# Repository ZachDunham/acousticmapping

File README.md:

acousticmapping
===============

Data vis, light painting mashup exploring room acoustics 

## Synopsis 
The goal for this project is to be able to photograph standing wave interference to create a kind of acoustical map of a room. Wave interference, simply put, is caused when two waves of the same frequency but different phase combine and result in a waveform that has an increased or decreased amplitude. 

In order to photograph these interference or standing wave patterns, I'm playing a range of sine tones but only working with one frequency at a time in order to isolate these interferences. In any listening situation there are direct and reflected sounds. As sound leaves the source it propagates outward, reflecting off of surfaces along the way, until it reaches your ears. Depending on where you are in the room, some portion of this sound also travels directly to the ear. Because of these alternate routes (reflected and direct) we end up with differences in arrival time which can also mean differences in the phase (angle) of the wave. As these in- or out-of-phase signals reach our ear, they can cancel each other out or combine to result in a larger waveform.

The hardware and software here are part of this ongoing project.  

## Liscense 
In the interest of collaboration and good will, the files herein are offered for public use. Just don't be a jerk about it and credit me if you use it commercially :)

## CONTAINED HEREIN
* Embedded systems design files: Namely .brd, .sch
* Firmware: Arduino sketches

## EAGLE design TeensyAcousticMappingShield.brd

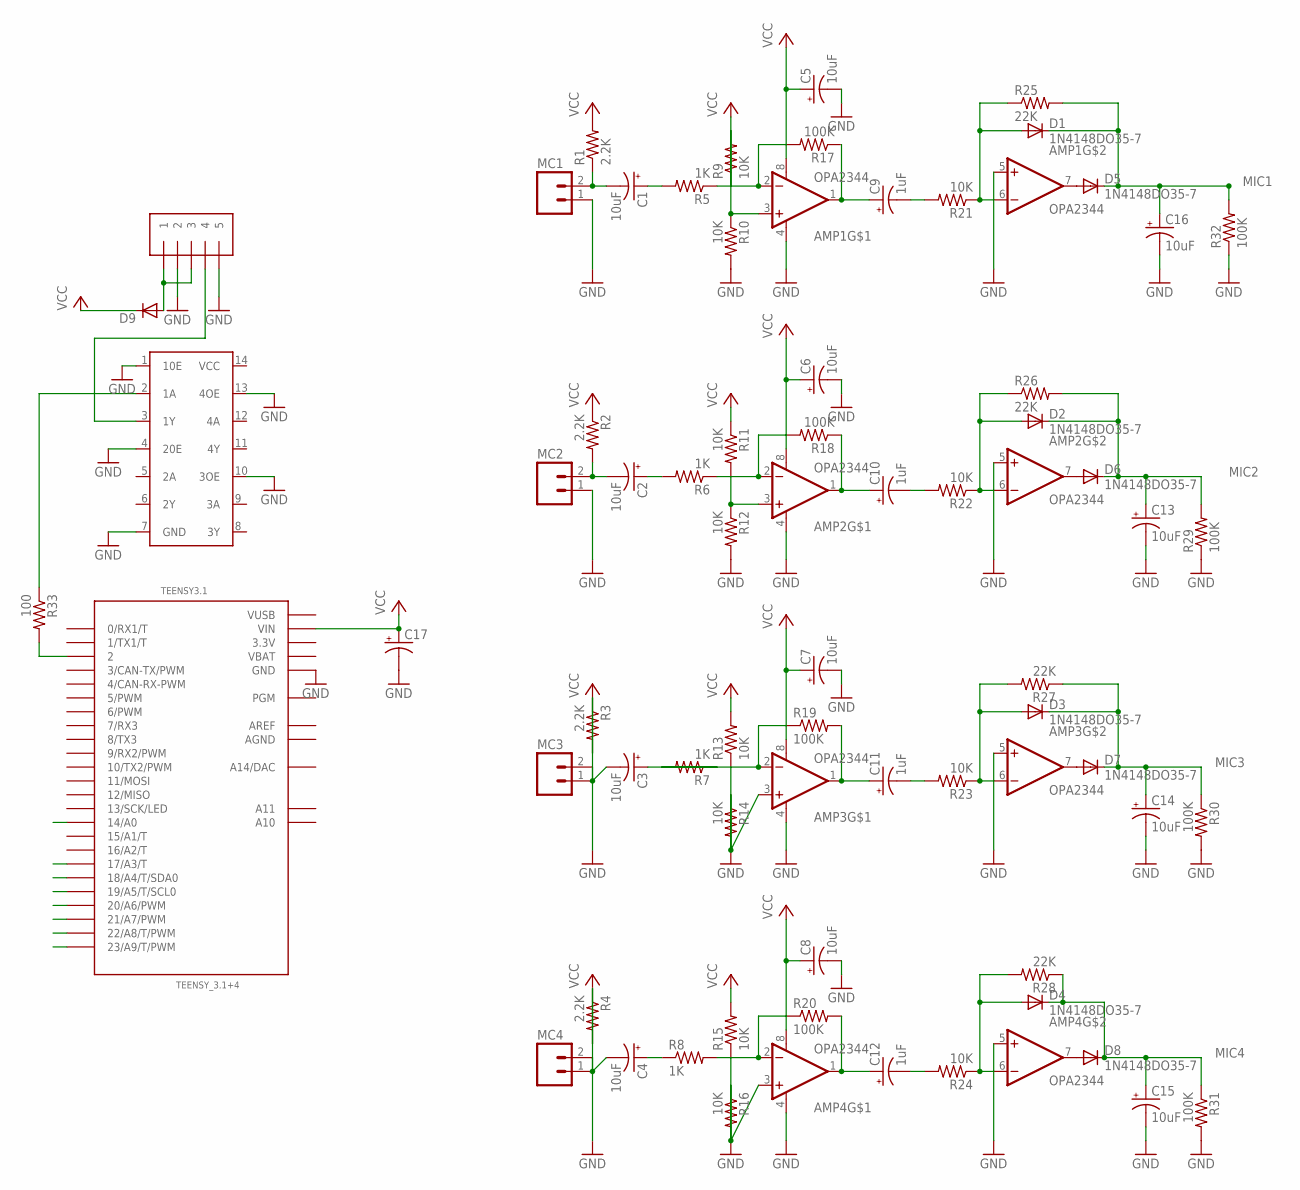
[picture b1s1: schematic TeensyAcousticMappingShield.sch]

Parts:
AMP1, AMP2, AMP3, AMP4: OPA2344; DIP08
C1, C2, C3, C4, C5, C6, C7, C8, C13, C14, C15, C16: 10uF; E2-4
C9, C10, C11, C12: 1uF; E2-4
C17: CPOL-USE2.5-6; E2,5-6
D1, D2, D3, D4, D5, D6, D7, D8: 1N4148DO35-7; DO35-7
D9: DIODE-C1702-05; C1702-05
IO: 1X5; 1X05-3.5MM
LEVELSHIFT: 74AHCT125; DIL14
MC1, MC2, MC3, MC4: M02LOCK_LONGPADS; 1X02_LOCK_LONGPADS
R1, R2, R3, R4: 2.2K; 0207/2V
R5, R6, R7, R8: 1K; 0207/2V
R9, R10, R11, R12, R13, R14, R15, R16, R21, R22, R23, R24: 10K; 0207/2V
R17, R18, R19, R20, R29, R30, R31, R32: 100K; 0207/2V
R25, R26, R27, R28: 22K; 0207/2V
R33: 100; 0207/2V
TEENSY3.1: TEENSY_3.1+4

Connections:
3.3V: TEENSY3.1.3.3V, TEENSY3.1.3.3V1 (3.3V)
AGND: TEENSY3.1.AGND
AREF: TEENSY3.1.AREF
B+: D9.A, IO.1, IO.3
GND: AMP1.4 (V-), AMP1.5 (+IN), AMP2.4 (V-), AMP2.5 (+IN), AMP3.4 (V-), AMP3.5 (+IN), AMP4.4 (V-), AMP4.5 (+IN), C5.-, C6.-, C7.-, C8.-, C13.-, C14.-, C15.-, C16.-, C17.-, IO.2, IO.5, LEVELSHIFT.1 (10E), LEVELSHIFT.4 (20E), LEVELSHIFT.7 (GND), LEVELSHIFT.10 (3OE), LEVELSHIFT.13 (4OE), MC1.1, MC2.1, MC3.2, MC4.2, R10.2, R12.2, R14.1, R16.1, R29.1, R32.1, TEENSY3.1.GND, TEENSY3.1.GND1 (GND)
MIC1: C16.+, D1.C, D5.C, R25.2, R32.2, TEENSY3.1.14/A0
MIC2: C13.+, D2.C, D6.C, R26.2, R29.2, TEENSY3.1.17/A3 (17/A3/T)
MIC3: C14.+, D3.C, D7.C, R27.1, R30.1, TEENSY3.1.18/A4 (18/A4/T/SDA0)
MIC4: C15.+, D4.C, D8.C, R28.1, R31.1, TEENSY3.1.19/A5 (19/A5/T/SCL0)
unnamed: AMP1.3 (+IN), R9.2, R10.1
unnamed: AMP1.2 (-IN), R5.1, R17.2
unnamed: AMP1.1 (OUT), C9.+, R17.1
unnamed: C1.+, R5.2
unnamed: C1.-, MC1.2, R1.1
unnamed: C9.-, R21.2
unnamed: AMP1.6 (-IN), D1.A, R21.1, R25.1
unnamed: AMP1.7 (OUT), D5.A
unnamed: AMP2.3 (+IN), R11.2, R12.1
unnamed: AMP2.2 (-IN), R6.1, R18.2
unnamed: AMP2.1 (OUT), C10.+, R18.1
unnamed: C2.+, R6.2
unnamed: C2.-, MC2.2, R2.2
unnamed: C10.-, R22.2
unnamed: AMP2.6 (-IN), D2.A, R22.1, R26.1
unnamed: AMP2.7 (OUT), D6.A
unnamed: AMP3.3 (+IN), R13.1, R14.2
unnamed: R33.2, TEENSY3.1.2
unnamed: LEVELSHIFT.2 (1A), R33.1
unnamed: AMP3.2 (-IN), R7.2, R19.1
unnamed: AMP3.1 (OUT), C11.+, R19.2
unnamed: C3.+, R7.1
unnamed: C3.-, MC3.1, R3.1
unnamed: C11.-, R23.2
unnamed: AMP3.6 (-IN), D3.A, R23.1, R27.2
unnamed: AMP3.7 (OUT), D7.A
unnamed: AMP4.3 (+IN), R15.1, R16.2
unnamed: AMP4.2 (-IN), R8.2, R20.1
unnamed: AMP4.1 (OUT), C12.+, R20.2
unnamed: C4.+, R8.1
unnamed: C4.-, MC4.1, R4.1
unnamed: C12.-, R24.2
unnamed: AMP4.6 (-IN), D4.A, R24.1, R28.2
unnamed: AMP4.7 (OUT), D8.A
unnamed: IO.4, LEVELSHIFT.3 (1Y)
VBAT: TEENSY3.1.VBAT
VCC: AMP1.8 (V+), AMP2.8 (V+), AMP3.8 (V+), AMP4.8 (V+), C5.+, C6.+, C7.+, C8.+, C17.+, D9.C, R1.2, R2.1, R3.2, R4.2, R9.1, R11.1, R13.2, R15.2, TEENSY3.1.VIN
VUSB: TEENSY3.1.VUSB

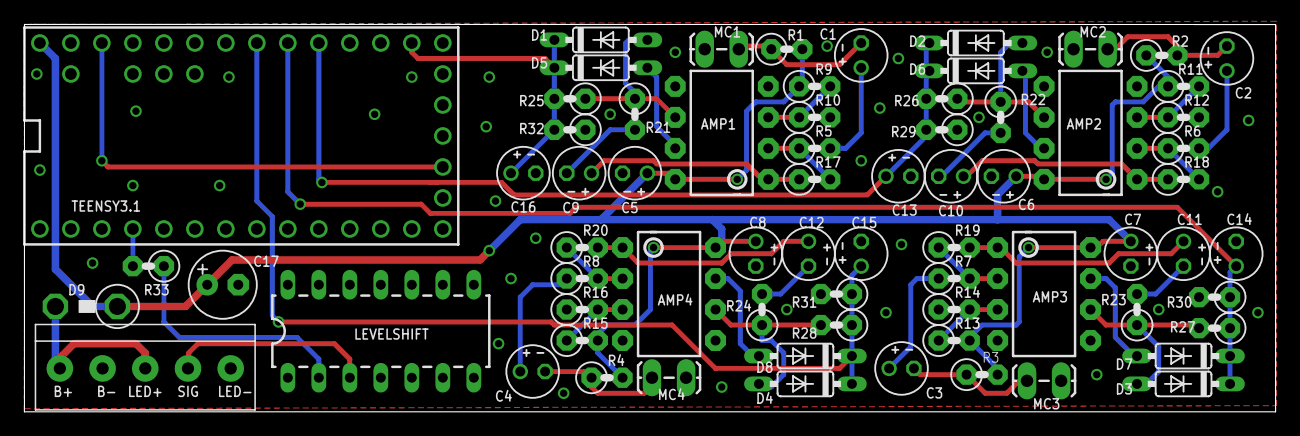
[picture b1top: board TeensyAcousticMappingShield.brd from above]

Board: 2 copper layers, 102.5 x 31.8 mm, 70 parts (0 on the bottom side), 43 nets.

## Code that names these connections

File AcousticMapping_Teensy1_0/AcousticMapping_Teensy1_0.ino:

#include <OctoWS2811.h>

const int ledsPerStrip = 144;

DMAMEM int displayMemory[ledsPerStrip*6];
int drawingMemory[ledsPerStrip*6];

const int config = WS2811_GRB | WS2811_800kHz;

OctoWS2811 leds(ledsPerStrip, displayMemory, drawingMemory, config);

const int num_lights = 144;
const int num_mics = 4;
const int brightness_steps = 4;

int val = 0;                                   // value to store mic1
int val2 = 0;                                  // value to store mic2 
int val3 = 0;                                  // value to store mic 3
int val4 = 0;                                  //value to store mic 4
// colors 
int r = 30;                                      // red value 
int g = 0;                                   // green value
int b = 30;                                    // blue value

int ressteps = 100;

int smoothedVal     = 0;    // smoothed result
int smoothedVal2     = 0;    // smoothed result
int smoothedVal3     = 0;    // smoothed result
int smoothedVal4     = 0;    // smoothed result
int samples         = 4;    // amount of samples

const int mic = 3;      // pin that mic1 is attached to
const int mic2 = 4;      // pin that mic2 is attached to 
const int mic3 = 5;      // pin that mic3 is attached to 
const int mic4 = 8;      // pin that mic4 is attached to 


const int ledPin = 9;           // pin that the LED is attached to
const int indicatorLedPin = 13; // pin that the built-in LED is attached to
const int buttonPin = 8;        // pin that the button is attached to


// These variables will change:
int sensorMin = 1023;  // minimum sensor value
int sensorMin2 = 1023;  // minimum sensor value2
int sensorMin3 = 1023;  // minimum sensor value3
int sensorMin4 = 1023;  // minimum sensor value4

int sensorMax = 0;     // maximum sensor value
int sensorMax2 = 0;    // maximum sensor value2
int sensorMax3 = 0;     // maximum sensor value3
int sensorMax4 = 0;     // maximum sensor value4

int ledsize = (num_lights / num_mics); //size of without the * i

void setup() {
  leds.begin();          // initialize pixel strip
  leds.show();           // Initialize all pixels to 'off'
  pinMode(indicatorLedPin, OUTPUT);
  pinMode (ledPin, OUTPUT);
  pinMode (buttonPin, INPUT);
  Serial.begin(9600);
  
  //calibrate mic's min and max here
  
  for(int c=0; c<1000000; c++){
  digitalWrite(indicatorLedPin, HIGH);
    val = analogRead(mic);
    val2 = analogRead(mic2);
    val3 = analogRead(mic3);
    val4 = analogRead(mic4);
    // record the maximum/minimum sensor value1
    if (val > sensorMax) {
    sensorMax = val;
    }
    if (val < sensorMin) {
    sensorMin = val;
    }
    // record the maximum/minimum sensor value2
    if (val2 > sensorMax2) {
    sensorMax2 = val2;
    }
    if (val2 < sensorMin2) {
    sensorMin2 = val2;
    }
    // record the maximum/minimum sensor value3
    if (val3 > sensorMax3) {
    sensorMax3 = val3;
    }
    if (val3 < sensorMin3) {
    sensorMin3 = val3;
    }
    // record the maximum/minimum sensor value4
    if (val4 > sensorMax4) {
    sensorMax4 = val4;
    }
    if (val4 < sensorMin4) {
    sensorMin4 = val4;
    }
  }
  //done calibrating 
  digitalWrite(indicatorLedPin, LOW);
}

void loop() {

  //mic 1 
 val = running_Average(mic);  // smooth the mic readings with Running Average function
 val = map(val, sensorMin, sensorMax/2, 0, ressteps);  // map the range to 0-255
 val = constrain(val, 0, ressteps);
 Serial.println(val); // for debugging 
 newledRange(val, 1); 
 //mic2
 val2 = running_Average2(mic2);  // smooth the mic readings with Running Average function
 val2 = map(val2, sensorMin2, sensorMax2, 0, ressteps);  // map the range to 0-255
 val2 = constrain(val2, 0, ressteps);
 newledRange(val2, 2); 

 //mic3
 val3 = running_Average3(mic3);  // smooth the mic readings with Running Average function
 val3 = map(val3, sensorMin3, sensorMax3, 0, ressteps);  // map the range to 0-255
 val3 = constrain(val3, 0, ressteps);
 newledRange(val3, 3); 
 //mic4
 val4 = running_Average4(mic4);  // smooth the mic readings with Running Average function
 val4 = map(val4, sensorMin4, sensorMax4, 0, ressteps);  // map the range to 0-255
 val4 = constrain(val4, 0, ressteps);
 newledRange(val4, 4); 
 
leds.show();                               // refresh the strip

}
//average mic1
int running_Average(int microphone) {
  // read the value from the sensor
  // the range from an analog input is 0 - 1023
 int sensorVal = analogRead(microphone); 
 
  smoothedVal = smoothedVal + ((sensorVal - smoothedVal)/samples);

  return smoothedVal; 
 
}
//average mic2
int running_Average2(int microphone) {
  // read the value from the sensor
  // the range from an analog input is 0 - 1023
  int sensorVal = analogRead(microphone); 
 
  smoothedVal2 = smoothedVal2 + ((sensorVal - smoothedVal2)/samples);

  return smoothedVal2; 
 
}
//average mic3
int running_Average3(int microphone) {
  // read the value from the sensor
  // the range from an analog input is 0 - 1023
  int sensorVal = analogRead(microphone); 
 
  smoothedVal3 = smoothedVal3 + ((sensorVal - smoothedVal3)/samples);

  return smoothedVal3; 
 
}
//average mic4
int running_Average4(int microphone) {
  // read the value from the sensor
  // the range from an analog input is 0 - 1023
  int sensorVal = analogRead(microphone); 
 
  smoothedVal4 = smoothedVal4 + ((sensorVal - smoothedVal4)/samples);

  return smoothedVal4; 
 
}

void newledRange(int mappedval, int mic_num) {
  int rangemax = (ledsize * mic_num) -1;
  int rangemin = (ledsize * mic_num) - ledsize;
  boolean usemidpoint = false;
  int midpoint;
  int midpointlow;
  int midpointhigh;
 
  if (ledsize % 2 == 0){
    usemidpoint = true;
    midpoint = rangemin + (ledsize/2) -1; //15,45 when num_mics =
    }
  
    else{
      midpointlow = floor(ledsize/2) + rangemin - 1; 
      midpointhigh = midpointlow + 1; //ceil(ledsize/2) + rangemin - 1
       }
  
  int strength = (((mappedval * ledsize) / ressteps) / 2); // x gives a ratio of mappedval to the size of the set //MAKE SIZE OF MIDPOINT INSTEAD!!!
  //int brightness = setbrightness(mappedval);
  /*
  int strength_steps = brightness_steps * strength;//(ledsize/2);
  const int brightness_percent = 255/brightness_steps;
  int x = 0;
  
  for ( int i = 1; i <= strength_steps; i++ ) {
    int mod = i % brightness_steps;
   int brightness = map(mod, 0, brightness_steps-1, brightness_percent, 255); 
      if ( mod == 0 ){
        x++;
      }
      */
     // Serial.println(midpoint);
      turnoffleds(rangemin, rangemax);
      if ( usemidpoint == true ) {
        for(int i=midpoint; i<midpoint+strength; i++){
        leds.setPixel(i, 30, 30, 0);
        }
          for(int j=midpoint; j>midpoint-strength; --j){
            leds.setPixel(j, 30, 30, 0);
            }
      } 
       else {
         for(int i=midpoint; i<midpoint+strength; i++){
           leds.setPixel(i, 30, 30, 0);
            }
         for(int j=midpoint; j>midpoint-strength; --j){
           leds.setPixel(j, 30, 30, 0);
           }
      }
      
     
  //}
  
}

void turnoffleds(int rangemin, int rangemax) {
  for ( int i = rangemin; i <= rangemax; i++ ) {
    leds.setPixel(i, 0, 0, 0);
    } 
}
  

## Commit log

2014-07-23 Acoustic Mapping, Initial Commit
    Latest board and schematic files for the teensy breakout as well as the
    current teensyduino sketch I’m running (somewhat successfully).
2014-09-08 Acoustic Mapping
    Updated code for the custom teensy breakout

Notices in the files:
parts and their libraries:
SparkFun-Connectors: Licensing: CC v3.0 Share-Alike You are welcome to use this library for commercial purposes.
